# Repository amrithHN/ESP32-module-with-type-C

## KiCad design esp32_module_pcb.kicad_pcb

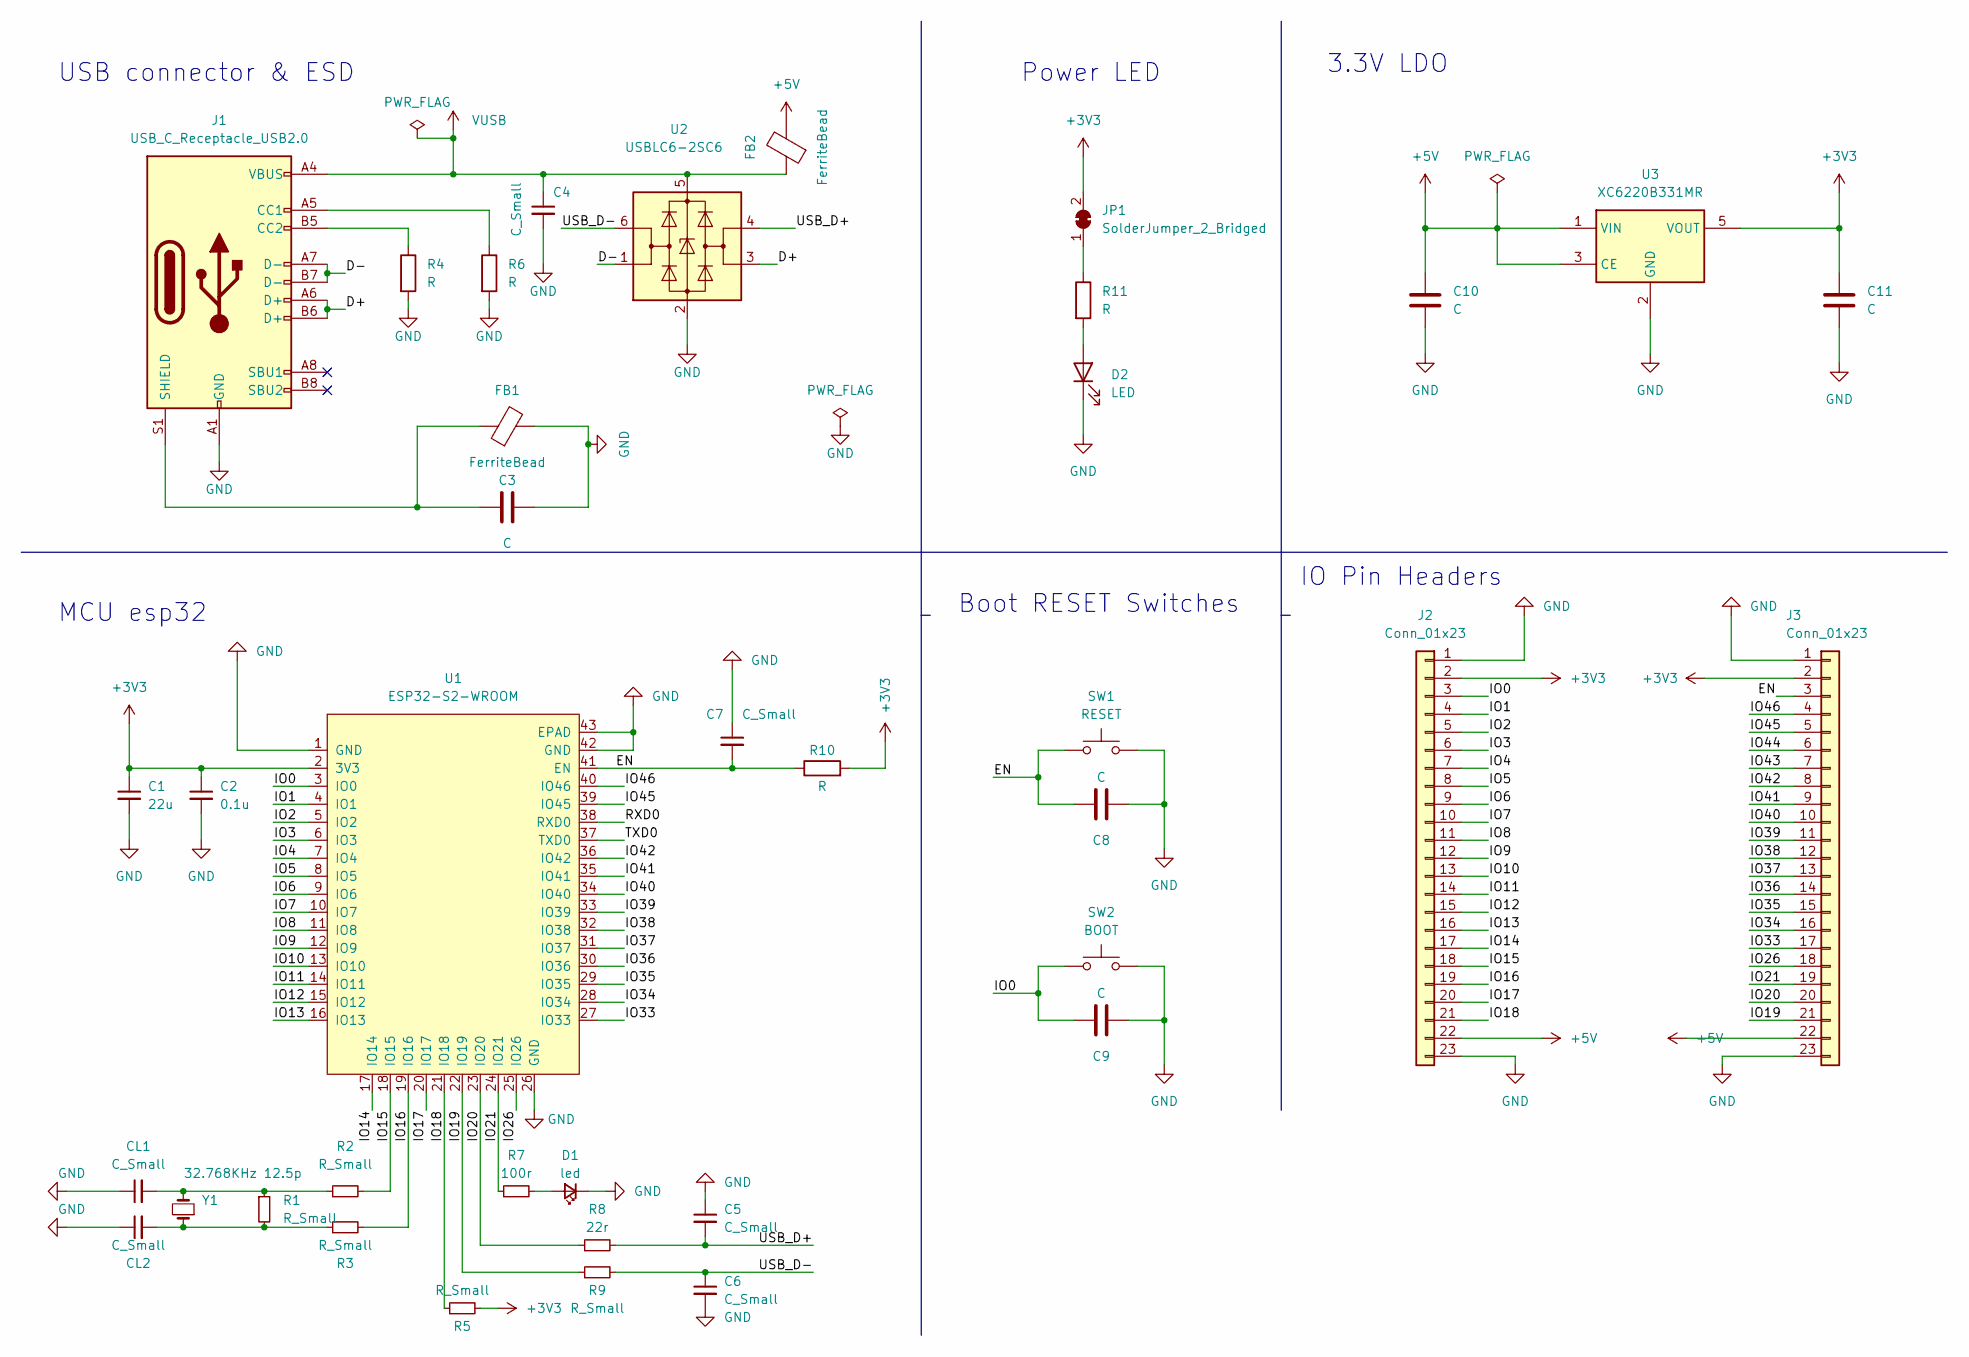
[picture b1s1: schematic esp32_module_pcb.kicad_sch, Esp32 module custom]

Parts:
C1: 22u; C_0603_1608Metric
C2: 0.1u; C_0603_1608Metric
C3, C8, C9, C10, C11: C; C_0603_1608Metric
C4, C5, C6, C7: C_Small; C_0603_1608Metric
CL1, CL2: C_Small; C_0603_1608Metric
D1: led; LED_0603_1608Metric
D2: LED; LED_0603_1608Metric
FB1, FB2: FerriteBead; L_0603_1608Metric
J1: USB_C_Receptacle_USB2.0; USB_C_Receptacle_HRO_TYPE-C-31-M-12
J2, J3: Conn_01x23; PinHeader_1x23_P2.54mm_Vertical
JP1: SolderJumper_2_Bridged; SolderJumper-2_P1.3mm_Bridged2Bar_RoundedPad1.0x1.5mm
R1, R2, R3, R5, R9: R_Small; R_0603_1608Metric
R4, R6, R10, R11: R; R_0603_1608Metric
R7: 100r; R_0603_1608Metric
R8: 22r; R_0603_1608Metric
SW1: RESET; Alps_SKRK
SW2: BOOT; Alps_SKRK
U1: ESP32-S2-WROOM
U2: USBLC6-2SC6; SOT-23-6
U3: XC6220B331MR; SOT-23-5
Y1: 32.768KHz 12.5p; Crystal_SMD_3215-2Pin_3.2x1.5mm

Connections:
+3V3: C1.1, C2.1, C11.1, J2.2, J3.2, JP1.2 (B), R5.2, R10.2, U1.2 (3V3), U3.5 (VOUT)
+5V: C10.1, FB2.2, J2.22, J3.22, U3.1 (VIN), U3.3 (CE)
/D+: J1.A6 (D+), J1.B6 (D+), U2.3 (I/O2)
/D-: J1.A7 (D-), J1.B7 (D-), U2.1 (I/O1)
/EN: C7.2, C8.1, J3.3, R10.1, SW1.1, U1.41 (EN)
/IO0: C9.1, J2.3, SW2.1, U1.3 (IO0)
/IO1: J2.4, U1.4 (IO1)
/IO2: J2.5, U1.5 (IO2)
/IO3: J2.6, U1.6 (IO3)
/IO4: J2.7, U1.7 (IO4)
/IO5: J2.8, U1.8 (IO5)
/IO6: J2.9, U1.9 (IO6)
/IO7: J2.10, U1.10 (IO7)
/IO8: J2.11, U1.11 (IO8)
/IO9: J2.12, U1.12 (IO9)
/IO10: J2.13, U1.13 (IO10)
/IO11: J2.14, U1.14 (IO11)
/IO12: J2.15, U1.15 (IO12)
/IO13: J2.16, U1.16 (IO13)
/IO14: J2.17, U1.17 (IO14)
/IO15: J2.18, R2.2, U1.18 (IO15)
/IO16: J2.19, R3.2, U1.19 (IO16)
/IO17: J2.20, U1.20 (IO17)
/IO18: J2.21, R5.1, U1.21 (IO18)
/IO19: J3.21, R9.1, U1.22 (IO19)
/IO20: J3.20, R8.1, U1.23 (IO20)
/IO21: J3.19, R7.1, U1.24 (IO21)
/IO26: J3.18, U1.25 (IO26)
/IO33: J3.17, U1.27 (IO33)
/IO34: J3.16, U1.28 (IO34)
/IO35: J3.15, U1.29 (IO35)
/IO36: J3.14, U1.30 (IO36)
/IO37: J3.13, U1.31 (IO37)
/IO38: J3.12, U1.32 (IO38)
/IO39: J3.11, U1.33 (IO39)
/IO40: J3.10, U1.34 (IO40)
/IO41: J3.9, U1.35 (IO41)
/IO42: J3.8, U1.36 (IO42)
/IO43: J3.7
/IO44: J3.6
/IO45: J3.5, U1.39 (IO45)
/IO46: J3.4, U1.40 (IO46)
/RXD0: U1.38 (RXD0)
/TXD0: U1.37 (TXD0)
/USB_D+: C5.2, R8.2, U2.4 (I/O2)
/USB_D-: C6.1, R9.2, U2.6 (I/O1)
GND: C1.2, C2.2, C3.2, C4.2, C5.1, C6.2, C7.1, C8.2, C9.2, C10.2, C11.2, CL1.1, CL2.1, D1.1 (K), D2.1 (K), FB1.2, J1.A1 (GND), J1.A12 (GND), J1.B1 (GND), J1.B12 (GND), J2.1, J2.23, J3.1, J3.23, R4.2, R6.2, SW1.2, SW2.2, U1.1 (GND), U1.26 (GND), U1.42 (GND), U1.43 (EPAD), U2.2 (GND), U3.2 (GND)
unnamed: C3.1, FB1.1, J1.S1 (SHIELD)
unnamed: CL1.2, R1.1, R2.1, Y1.2
unnamed: CL2.2, R1.2, R3.1, Y1.1
unnamed: D1.2 (A), R7.2
unnamed: D2.2 (A), R11.2
unnamed: J1.A5 (CC1), R6.1
unnamed: J1.B5 (CC2), R4.1
unnamed: JP1.1 (A), R11.1
VUSB: C4.1, FB2.1, J1.A4 (VBUS), J1.A9 (VBUS), J1.B4 (VBUS), J1.B9 (VBUS), U2.5 (VBUS)

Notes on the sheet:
MCU esp32
Power LED
Boot RESET Switches
USB connector & ESD
3.3V LDO
IO Pin Headers

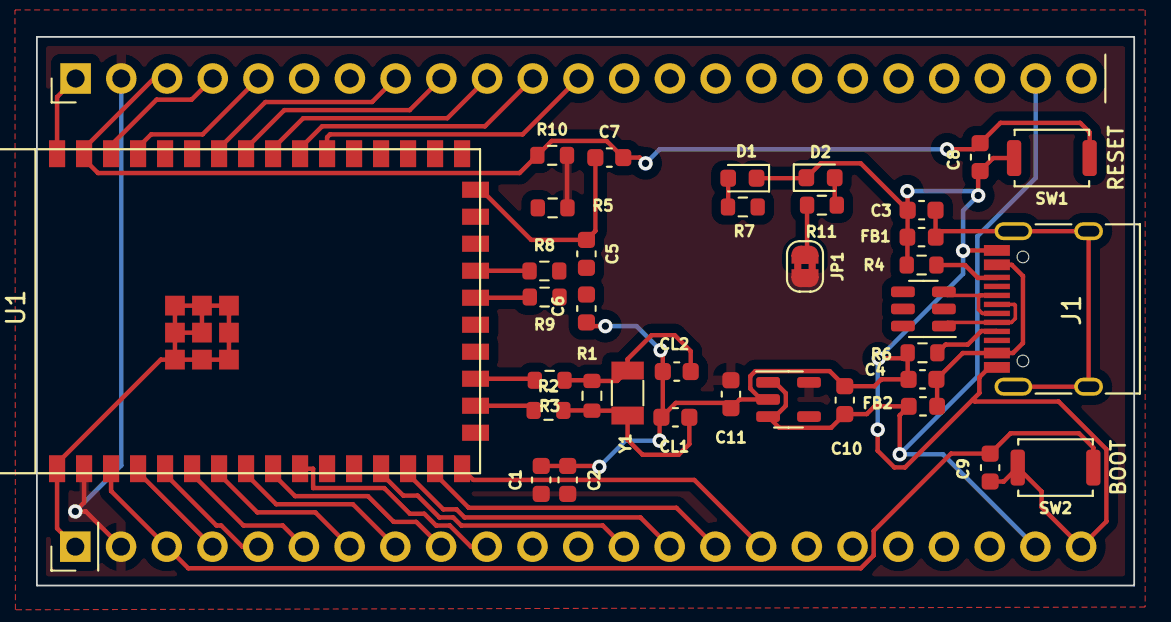
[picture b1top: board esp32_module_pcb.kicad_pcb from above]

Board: 2 copper layers, 61.0 x 30.5 mm, 38 parts (0 on the bottom side), 52 nets.

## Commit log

2022-06-16 added image
